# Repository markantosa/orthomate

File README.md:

# EPD 3D G6 — Orthomate

Battery-powered adaptive orthopedic insole controller. Redistributes plantar pressure in real-time using three micro linear stepper actuators driven by force sensor feedback. Includes a BLE companion Android app for live monitoring.

> **🏆 Winner — Top Course Project, EPD 3D Exhibition April 2026**

## Hardware at a glance

| Component | Detail |
|-----------|--------|
| MCU | ESP32-C6 SuperMini |
| Stepper drivers | 3× TMC2209 (STEP/DIR mode, ENN hardwired LOW on PCB) |
| Actuators | 3× micro linear bipolar stepper |
| Pressure sensors | 4× FSR (R1 1kΩ + C 100nF RC filter per channel, R2 10kΩ pull-down) |
| Display | 0.91" OLED (SSD1306, I2C) |
| Charger | TP4056 Type-C |
| Boost converter | XL6009 → 5 V system rail |
| Battery | 1S LiPo 2000–3000 mAh |
| User input | 1× momentary mode button |
| BLE | NimBLE-Arduino 2.5.0 — advertises as `EPD3DG6` |

## PCB placement

Orthomate uses two custom PCBs that work together inside a modified shoe:

**Controller PCB** — mounts in a controller module. Houses the ESP32-C6, three TMC2209 stepper drivers, TP4056 charger, XL6009 boost converter, and the 20-pin connector (J9) to the insole. The LiPo battery sits alongside it.

**Insole PCB** — sits directly underfoot inside the shoe. Hosts the three FSR pressure-sensing zones (metatarsal, arch, calcaneus) and the three micro linear stepper actuator assemblies. The actuators extend upward to redistribute localised plantar pressure. Connects back to the controller PCB via a 20-pin ribbon/wire harness.

## Exhibition highlights

### Final product

### ANSYS stress analysis

### Exhibition day

### Poster

### Downloadable resources

- [Orthomate Final Slides (PDF)](Exhibition%20Files%20and%20Photos/Orthomate%20Final%20Slides.pdf)
- [Orthomate Poster (PDF)](Exhibition%20Files%20and%20Photos/Orthomate%20Poster.pdf)

## Repository structure

```
orthomate/
├── Electronics Reference.txt           # Hardware design spec (v6.0)
├── BOM.txt                             # Bill of materials
├── firmware/
│   ├── main/                           # Full operational firmware (PlatformIO)
│   │   ├── platformio.ini
│   │   └── src/main.cpp
│   ├── ARDUINO IDE MAIN/               # Arduino IDE version of the full firmware
│   │   └── EPD3DG6_Main/EPD3DG6_Main.ino
│   ├── ARDUINO IDE APP TEST/           # Minimal Arduino IDE sketch for BLE app testing
│   │   └── sketch_apr14a/sketch_apr14a.ino
│   ├── stepper_test/                   # Single-axis stepper back-and-forth smoke test
│   ├── homing_test/                    # Blind homing: retract to min, extend to 12 mm
│   ├── button_test/                    # Button + OLED input test
│   └── oled_test/                      # OLED display test
├── android_app/                        # Kotlin/Compose BLE companion app
│   └── app/src/main/AndroidManifest.xml
├── Controller PCB KiCad Files/         # KiCad schematic + layout for controller PCB
├── Controller PCB Iterations/          # Gerber files from each revision (V2–V5)
├── Insole PCB KiCad Files/             # KiCad schematic + layout for insole PCB
├── Insole PCB Iterations/              # Gerber files from each revision
├── Exhibition Files and Photos/        # Exhibition media, poster, and slides
└── docs/
    ├── FIRMWARE_MAIN.md                # Detailed firmware walkthrough
    ├── FLASH_GUIDE.md                  # PlatformIO build & upload instructions
    ├── ANDROID_APP_GUIDE.md            # Android app build & sideload instructions
    └── TMC2209_CURRENT_TUNING.md
```

## Firmware — operational logic

The main firmware (`firmware/main/`) implements a full fitting cycle driven by one button:

```
DISCONNECTED ──[plug in]──► CONNECTED ──[btn]──► MEASURING
                                                      │ (auto)
                                                  MEASURED ──[btn]──► ACTUATING
                                                                           │ (auto)
                                                                         DONE ──[unplug]──► DISCONNECTED
                                                                         (insole retains shape)

On next plug-in with actuators extended:  DISCONNECTED ──► HOMING ──► CONNECTED
```

| Mode | Behaviour |
|------|-----------|
| **CONNECTED** | Idle; shows battery %, BLE status on OLED |
| **MEASURING** | Reads all 4 FSR channels, 7-sample median filter, computes relative load fractions |
| **ACTUATING** | Drives each actuator inversely proportional to region load — lowest load = largest extension |
| **DONE** | Holds position; unplug to use insole as-is |
| **HOMING** | Auto-triggered on reconnect when actuators are extended; retracts all to home |

Extension formula: $ext_i \propto (1 - r_i)$ where $r_i = F_i / \sum F$

## BLE — Android companion app

The ESP32 advertises a GATT service and notifies a JSON payload at ~4 Hz:

```json
{"fsr1": 42, "fsr2": 18, "fsr3": 75, "mode": "MEASURING", "batt": 67}
```

| BLE field | Value |
|-----------|-------|
| Device name | `EPD3DG6` |
| Service UUID | `4fa0c560-78a3-11ee-b962-0242ac120002` |
| Characteristic UUID | `4fa0c561-78a3-11ee-b962-0242ac120002` (NOTIFY + READ) |
| Notify rate | ~4 Hz (every 250 ms) |
| MTU | 185 bytes |

The Android app (`android_app/`) displays real-time FSR forces as animated colour circles, current mode, battery %, and BLE status. See [docs/ANDROID_APP_GUIDE.md](docs/ANDROID_APP_GUIDE.md) for build and install instructions.

## GPIO assignment (ESP32-C6 SuperMini, Hardware Ref v6.0)

| GPIO | Function |
|------|----------|
| 0 | FSR1 METATARSAL (ADC, 11 dB attenuation) |
| 1 | FSR2 ARCH (ADC, 11 dB attenuation) |
| 2 | FSR3 CALCANEUS (ADC, 11 dB attenuation) |
| 3 | FSR4 AUX (ADC, 11 dB attenuation) |
| 4 | MODE\_BUTTON (INPUT\_PULLUP) — boot-safe |
| 5 | VBAT\_SENSE (ADC1 ch5, 11 dB attenuation, 1:2 divider) |
| 6 | OLED SCL (I2C) |
| 7 | OLED SDA (I2C) |
| 14 | ACT3\_DIR ⚠ dead channel (stepper motor pad detached) |
| 15 | CONN\_DETECT (INPUT\_PULLDOWN) |
| 16 | ACT2\_STEP (arch actuator) |
| 17 | ACT2\_DIR (arch actuator) |
| 18 | ACT3\_STEP ⚠ dead channel (stepper motor pad detached) |
| 19 | ACT1\_DIR |
| 20 | ACT1\_STEP |

## Quick start

- **Flash firmware:** [docs/FLASH_GUIDE.md](docs/FLASH_GUIDE.md)
- **Install Android app:** [docs/ANDROID_APP_GUIDE.md](docs/ANDROID_APP_GUIDE.md)
- **Firmware internals:** [docs/FIRMWARE_MAIN.md](docs/FIRMWARE_MAIN.md)

## Design rules

- Charging and actuator operation are **mutually exclusive** — never simultaneous.
- Never start all 3 motors simultaneously — stagger motor starts by 75 ms.
- Sample FSRs only when motors are idle; use 7-sample median filtering with 4 ms settling per sample.
- ADC attenuation must be set to **11 dB** (`ADC_11db`) on all analog pins for correct readings at the operating voltage range.
- VBAT < 3.35 V → disable actuators; VBAT < 3.5 V → show low battery warning.
- OLED updates are content-cached — only redraws when text changes (prevents I2C writes during motor current spikes).

## License

MIT — see [LICENSE](LICENSE)

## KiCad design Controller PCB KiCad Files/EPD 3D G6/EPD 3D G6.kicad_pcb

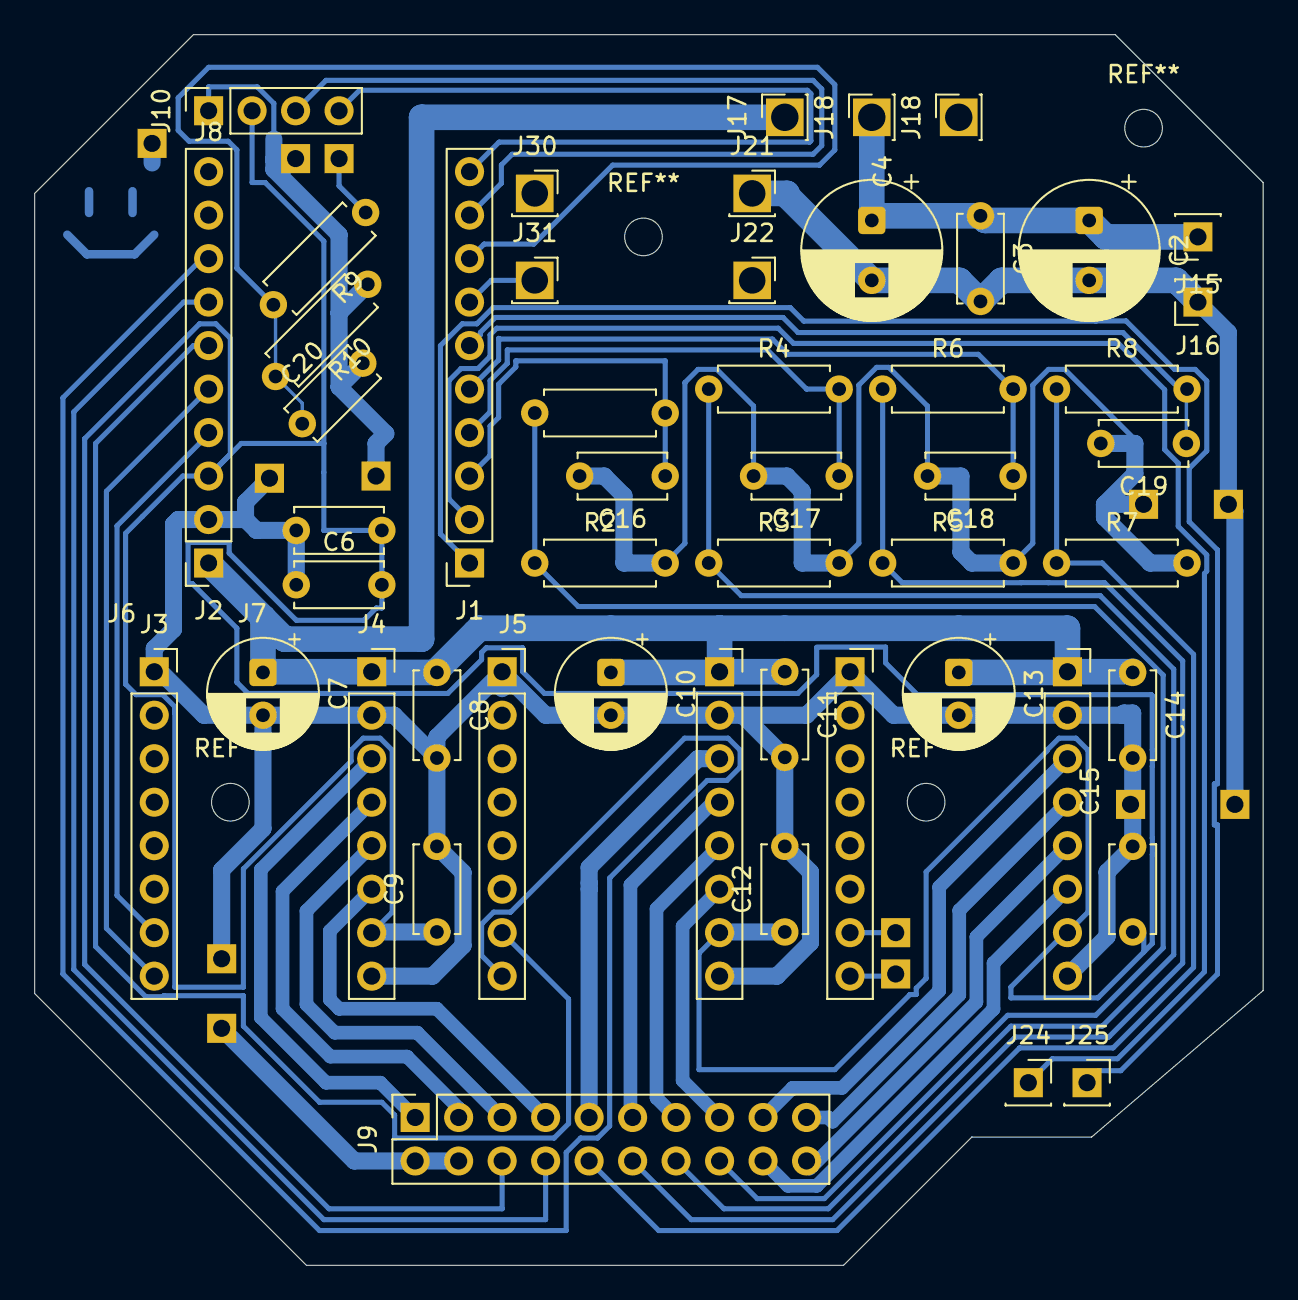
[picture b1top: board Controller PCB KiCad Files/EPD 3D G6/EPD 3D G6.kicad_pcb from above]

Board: 2 copper layers, 71.8 x 71.9 mm, 50 parts (0 on the bottom side), 34 nets.

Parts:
C2, C4: 470uF; CP_Radial_D8.0mm_P3.50mm
C3, C6, C8, C9, C11, C12, C14, C15, C16, C17, C18, C19, C20: 100nF; C_Disc_D5.0mm_W2.5mm_P5.00mm
C5: 10uF; C_Disc_D5.0mm_W2.5mm_P5.00mm
C7, C10, C13: 100uF; CP_Radial_D6.3mm_P2.50mm
J1: J_ESP32_L; PinSocket_1x10_P2.54mm_Vertical
J2: J_ESP32_R; PinSocket_1x10_P2.54mm_Vertical
J3: TMC2209_1_L; PinSocket_1x08_P2.54mm_Vertical
J4: TMC2209_1_R; PinSocket_1x08_P2.54mm_Vertical
J5: TMC2209_2_L; PinSocket_1x08_P2.54mm_Vertical
J6: TMC2209_2_R; PinSocket_1x08_P2.54mm_Vertical
J7: TMC2209_3_L; PinSocket_1x08_P2.54mm_Vertical
J8: TMC2209_3_R; PinSocket_1x08_P2.54mm_Vertical
J9: 20 PIN TO INSOLE; PinSocket_2x10_P2.54mm_Vertical
J10: OLED; PinSocket_1x04_P2.54mm_Vertical
J15: BOOST_OUT+; PinSocket_1x01_P2.54mm_Vertical
J16: BOOST_OUT-; PinSocket_1x01_P2.54mm_Vertical
J17: PWR+; PinSocket_1x01_P2.54mm_Vertical
J18, J18#2: PWR-; PinSocket_1x01_P2.54mm_Vertical
J21: BTN3; PinSocket_1x01_P2.54mm_Vertical
J22: BTN4; PinSocket_1x01_P2.54mm_Vertical
J24: ACT3_DIR; PinSocket_1x01_P2.54mm_Vertical
J25: ACT3_STEP; PinSocket_1x01_P2.54mm_Vertical
J30, J31: BTN1; PinSocket_1x01_P2.54mm_Vertical
R1, R4, R6, R8: 1k; R_Axial_DIN0207_L6.3mm_D2.5mm_P7.62mm_Horizontal
R2, R3, R5, R7: 10k; R_Axial_DIN0207_L6.3mm_D2.5mm_P7.62mm_Horizontal
R9, R10: 100k; R_Axial_DIN0207_L6.3mm_D2.5mm_P7.62mm_Horizontal

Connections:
3V3: C5.2, C6.2, C9.1, C12.1, C15.1, J2.3, J4.7, J6.7, J8.7, J9.6, J10.VCC
5V_SYS: C2.1, C3.1, C4.1, C7.1, C8.1, C10.1, C11.1, C13.1, C14.1, J2.1, J4.1, J6.1, J8.1, J15.1, J17.1, J18.1
ACT1_DIR: J2.5, J3.8
ACT1_OA1: J4.4, J9.3
ACT1_OA2: J4.3, J9.1
ACT1_OB1: J4.5, J9.5
ACT1_OB2: J4.6, J9.7
ACT1_STEP: J2.4, J3.7
ACT2_DIR: J2.8, J5.8
ACT2_OA1: J6.E, J9.11
ACT2_OA2: J6.3, J9.9
ACT2_OB1: J6.5, J9.13
ACT2_OB2: J6.6, J9.15
ACT2_STEP: J2.6, J5.7
ACT3_DIR: J1.2, J7.8, J24.1
ACT3_OA1: J8.4, J9.19
ACT3_OA2: J8.3, J9.17
ACT3_OB1: J8.5, J9.20
ACT3_OB2: J8.6, J9.18
ACT3_STEP: J1.1, J7.7, J25.1
CONN_DETECT: J2.7, J9.8
FSR1: J9.16, R1.1, R2.1
FSR1_ADC: C16.1, J1.3, R1.2
FSR2: J9.14, R3.1, R4.1
FSR2_ADC: C17.1, J1.E, R4.2
FSR3: J9.12, R5.1, R6.1
FSR3_ADC: C18.1, J1.5, R6.2
FSR4: J9.10, R7.1, R8.1
FSR4_ADC: C19.1, J1.6, R8.2
GND: C2.2, C3.2, C4.2, C5.1, C6.1, C7.2, C8.2, C9.2, C10.2, C11.2, C12.2, C13.2, C14.2, C15.2, C16.2, C17.2, C18.2, C19.2, C20.2, J2.2, J3.ACT1_EN, J4.2, J4.8, J5.ACT2EN, J6.2, J6.8, J7.ACT3_EN, J8.2, J8.8, J9.2, J9.4, J10.GND (Pin_1_GND), J16.1, J21.1, R2.2, R3.2, R5.2, R7.2, R10.1
MODE_BTN: J1.7, J30.1, J31.1
OLED_SCL: J1.9, J10.OLED_SCL
OLED_SDA: J1.10, J10.OLED_SDA
VBAT_SENSE: C20.1, J1.8, R9.2, R10.2

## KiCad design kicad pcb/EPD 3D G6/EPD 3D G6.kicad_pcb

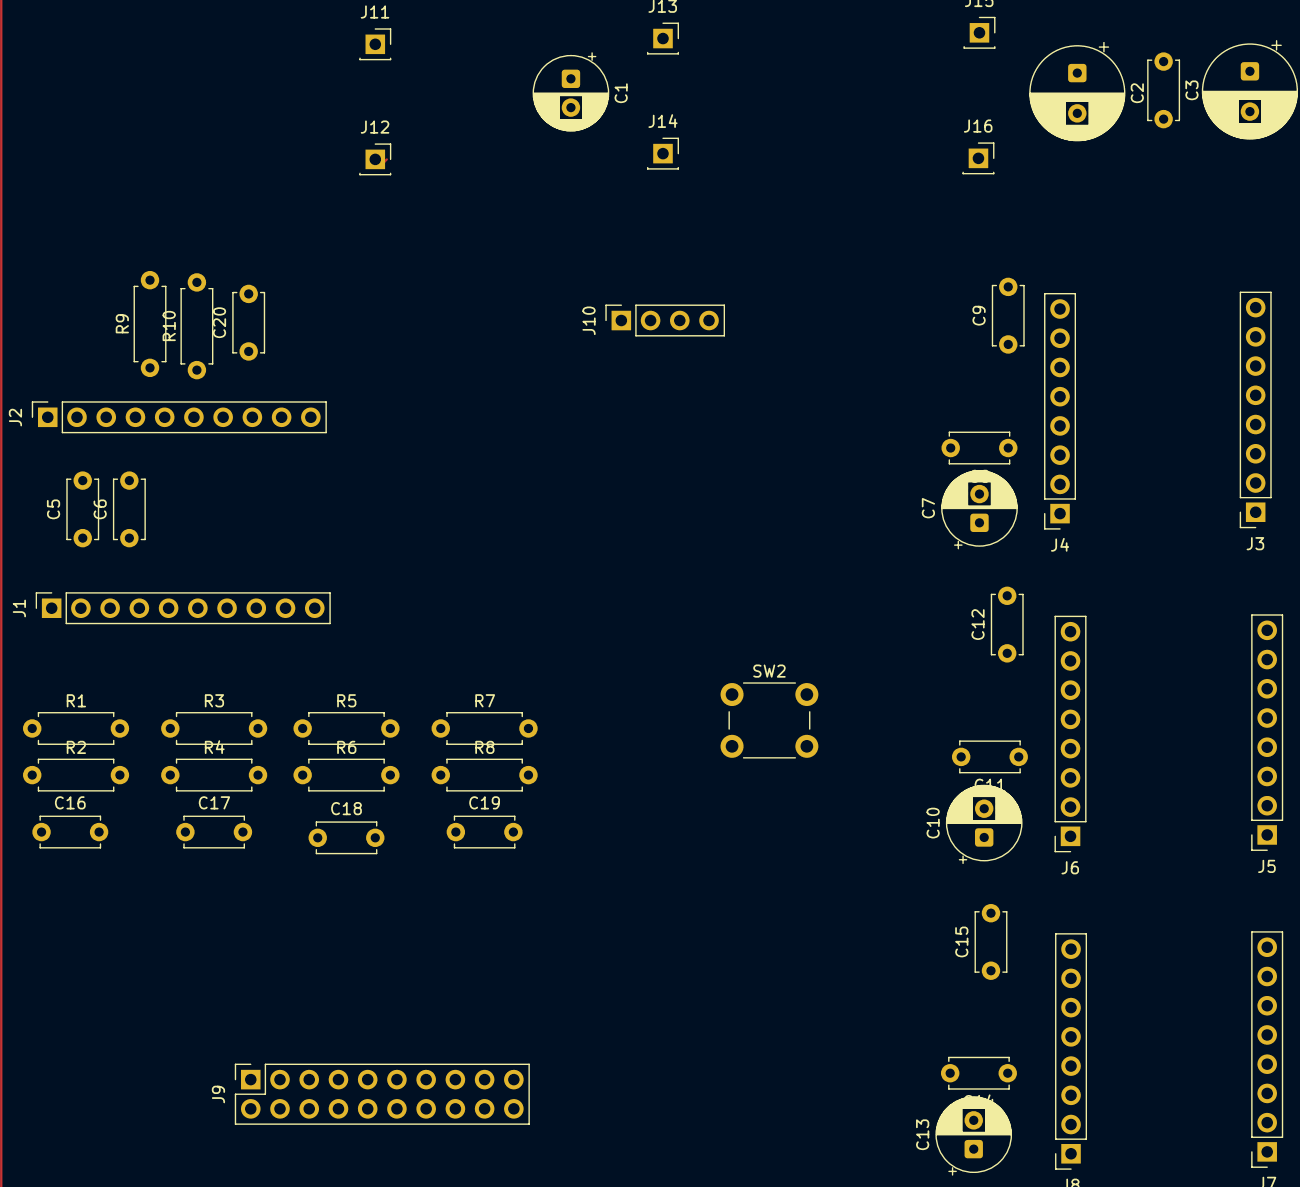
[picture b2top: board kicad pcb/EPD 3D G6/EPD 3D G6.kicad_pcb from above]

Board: 2 copper layers, 47 parts (0 on the bottom side), 13 nets.

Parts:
C1, C7, C10, C13: 100uF; CP_Radial_D6.3mm_P2.50mm
C2, C4: 470uF; CP_Radial_D8.0mm_P3.50mm
C3, C6, C8, C9, C11, C12, C14, C15, C16, C17, C18, C19, C20: 100nF; C_Disc_D5.0mm_W2.5mm_P5.00mm
C5: 10uF; C_Disc_D5.0mm_W2.5mm_P5.00mm
J1: J_ESP32_L; PinSocket_1x10_P2.54mm_Vertical
J2: J_ESP32_R; PinSocket_1x10_P2.54mm_Vertical
J3: TMC2209_1_L; PinSocket_1x08_P2.54mm_Vertical
J4: TMC2209_1_R; PinSocket_1x08_P2.54mm_Vertical
J5: TMC2209_2_L; PinSocket_1x08_P2.54mm_Vertical
J6: TMC2209_2_R; PinSocket_1x08_P2.54mm_Vertical
J7: TMC2209_3_L; PinSocket_1x08_P2.54mm_Vertical
J8: TMC2209_3_R; PinSocket_1x08_P2.54mm_Vertical
J9: 20 PIN TO INSOLE; PinSocket_2x10_P2.54mm_Vertical
J10: OLED; PinSocket_1x04_P2.54mm_Vertical
J11: BAT+; PinSocket_1x01_P2.54mm_Vertical
J12: BAT-; PinSocket_1x01_P2.54mm_Vertical
J13: BOOST_IN+; PinSocket_1x01_P2.54mm_Vertical
J14: BOOST_IN-; PinSocket_1x01_P2.54mm_Vertical
J15, J16: BOOST_OUT+; PinSocket_1x01_P2.54mm_Vertical
R1, R4, R6, R8: 1k; R_Axial_DIN0207_L6.3mm_D2.5mm_P7.62mm_Horizontal
R2, R3, R5, R7: 10k; R_Axial_DIN0207_L6.3mm_D2.5mm_P7.62mm_Horizontal
R9, R10: 100k; R_Axial_DIN0207_L6.3mm_D2.5mm_P7.62mm_Horizontal
SW2: SW_Push; SW_PUSH_6mm

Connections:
3V3: C5.2, C6.2, C9.1, C12.1, C15.1
5V_SYS: C2.1, C3.1, C4.1, C7.1, C8.1, C10.1, C11.1, C13.1, C14.1
FSR1: J9.5, R1.1, R2.1
FSR1_ADC: C16.1, R1.2
FSR2: J9.6, R3.1, R4.1
FSR2_ADC: C17.1, R4.2
FSR3: J9.7, R5.1, R6.1
FSR3_ADC: C18.1, R6.2
FSR4: J9.8, R7.1, R8.1
FSR4_ADC: C19.1, R8.2
GND: C2.2, C3.2, C4.2, C5.1, C6.1, C7.2, C8.2, C9.2, C10.2, C11.2, C12.2, C13.2, C14.2, C15.2, C16.2, C17.2, C18.2, C19.2, C20.2, J9.3, J9.4, R2.2, R3.2, R5.2, R7.2, R10.1, SW2.2
VBAT: C1.1, R9.1
VBAT_SENSE: C20.1, R9.2, R10.2

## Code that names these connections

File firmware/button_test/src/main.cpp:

/**
 * button_test — EPD 3D G6
 *
 * MODE button (GPIO4, INPUT_PULLUP, active LOW) triggers a sequence:
 *   Press → extend 5 s → retract 5 s → stop
 *
 * Wiring (Electronics Reference v5.0):
 *   GPIO 20 → ACT1_STEP
 *   GPIO 19 → ACT1_DIR
 *   GPIO 7  → OLED SDA
 *   GPIO 6  → OLED SCL
 *   GPIO 4  → MODE_BTN  (INPUT_PULLUP — do NOT hold at boot)
 *   ENN     → GND       (driver always enabled)
 */

#include <Arduino.h>
#include <Wire.h>
#include <Adafruit_GFX.h>
#include <Adafruit_SSD1306.h>

// ── Pins ─────────────────────────────────────────────────────────────────────
static constexpr uint8_t PIN_STEP = 20;
static constexpr uint8_t PIN_DIR  = 19;
static constexpr uint8_t PIN_BTN  = 4;   // MODE_BTN, active LOW
static constexpr uint8_t PIN_SDA  = 7;
static constexpr uint8_t PIN_SCL  = 6;

// ── OLED ─────────────────────────────────────────────────────────────────────
static Adafruit_SSD1306 gDisplay(128, 64, &Wire, -1);

static void oledShow(const char* status) {
    gDisplay.clearDisplay();
    gDisplay.setTextColor(SSD1306_WHITE);
    gDisplay.setTextSize(2);
    gDisplay.setCursor(0, 24);
    gDisplay.println(status);
    gDisplay.display();
}

// ── Motion ───────────────────────────────────────────────────────────────────
static constexpr uint32_t STEP_PULSE_US   = 20;    // step HIGH pulse width (µs)
static constexpr uint32_t STEP_START_US   = 16000; // starting step period (~60 steps/s)
static constexpr uint32_t STEP_MIN_US     = 4000;  // top-speed step period (~250 steps/s)
static constexpr uint32_t ACCEL_STEPS     = 200;   // steps to ramp from start to top speed
static constexpr uint32_t RUN_DURATION_MS = 5000;  // extend/retract time (ms)

// ── State ────────────────────────────────────────────────────────────────────
enum class RunState { IDLE, EXTENDING, RETRACTING };

static RunState gState        = RunState::IDLE;
static uint32_t gPhaseStart   = 0;
static uint32_t gLastStepUs   = 0;
static uint32_t gStepCount    = 0;   // steps taken in current phase (for ramp)
static bool     gLastBtn      = false;

// ── Helpers ──────────────────────────────────────────────────────────────────
static void motorStart(bool forward) {
    digitalWrite(PIN_DIR, forward ? HIGH : LOW);
    delayMicroseconds(100);
    gPhaseStart = millis();
    gLastStepUs = micros();
    gStepCount  = 0;
    oledShow(forward ? "EXTENDING" : "RETRACTING");
    Serial.printf("%s for %lus\n", forward ? "→ Extending" : "← Retracting", RUN_DURATION_MS / 1000);
}

static void motorStop() {
    oledShow("STOPPED");
    Serial.println("■ Stopped");
}

static void tickMotor() {
    // Linear ramp: interpolate period from STEP_START_US down to STEP_MIN_US
    uint32_t period = (gStepCount < ACCEL_STEPS)
        ? STEP_START_US - (uint32_t)((STEP_START_US - STEP_MIN_US) * gStepCount / ACCEL_STEPS)
        : STEP_MIN_US;

    uint32_t now = micros();
    if (now - gLastStepUs >= period) {
        digitalWrite(PIN_STEP, HIGH);
        delayMicroseconds(STEP_PULSE_US);
        digitalWrite(PIN_STEP, LOW);
        gLastStepUs = micros();
        gStepCount++;
    }
}

// ── Arduino entry points ─────────────────────────────────────────────────────
void setup() {
    Serial.begin(115200);
    delay(500);
    Serial.println("EPD 3D G6 — button test");
    Serial.printf("  Press -> extend %lus -> retract %lus\n", RUN_DURATION_MS / 1000, RUN_DURATION_MS / 1000);

    Wire.begin(PIN_SDA, PIN_SCL);
    gDisplay.begin(SSD1306_SWITCHCAPVCC, 0x3C);
    oledShow("STOPPED");

    pinMode(PIN_STEP, OUTPUT);
    pinMode(PIN_DIR,  OUTPUT);
    pinMode(PIN_BTN,  INPUT_PULLUP);

    digitalWrite(PIN_STEP, LOW);
    digitalWrite(PIN_DIR,  LOW);
}

void loop() {
    const bool pressed = (digitalRead(PIN_BTN) == LOW);

    switch (gState) {

        // ── Waiting for button press ──────────────────────────────────────────
        case RunState::IDLE:
            if (pressed && !gLastBtn) {  // rising edge only
                motorStart(true);
                gState = RunState::EXTENDING;
            }
            break;

        // ── Extending 5 s ────────────────────────────────────────────────────
        case RunState::EXTENDING:
            tickMotor();
            if (millis() - gPhaseStart >= RUN_DURATION_MS) {
                motorStart(false);
                gState = RunState::RETRACTING;
            }
            break;

        // ── Retracting 5 s ───────────────────────────────────────────
        case RunState::RETRACTING:
            tickMotor();
            if (millis() - gPhaseStart >= RUN_DURATION_MS) {
                motorStop();
                gState = RunState::IDLE;
            }
            break;
    }

    gLastBtn = pressed;
}

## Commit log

2026-04-01 Initial commit — hardware ref v4.1, operational firmware, LICENSE
2026-04-01 Add OLED test firmware (128x64 SSD1306, SCL=GPIO6, SDA=GPIO7)
2026-04-01 Add TMC2209 current limit tuning guide
2026-04-01 Add schematic framework (Phase A) - all 9 blocks, power rails, pin map, notes
2026-04-01 Reorganise schematic global labels for clean left-to-right power/signal flow
    - Power rails (VBAT, 5V_SYS, 3V3) moved to top of each block (Y=12-36)
    - ESP32 Block 3: inputs left side Y=30-90 (10mm steps), outputs right Y=30-110
    - TMC blocks 4A/4B/4C: power+signals stacked top-to-bottom within each block band
    - FSR/VBAT_SENSE/OLED/UI labels spread across full block height (no clustering)
    - Fixed label shapes: Block 3 input pins now correctly use 'input' shape (were 'output')
    - 48 global labels total, all named nets connect correctly
2026-04-01 Fix label positions: place all global_labels on block boundary edges
    Each label now sits exactly on its block's border (X=54/58/110/114/188/192/108/2)
    rather than floating in the middle of the sheet.
    - B1 VBAT output: right edge X=54
    - B2 VBAT in left X=58, 5V_SYS out right X=110
    - B3 ESP32: power at Y=9 top edge, 7 inputs on left X=114, 9 outputs on right X=188
    - B4A/4B/4C TMC: 5 inputs each on left X=192, distributed within Y bands
2026-04-02 Update all docs and firmware to Electronics Reference v5.0
    GPIO changes (v4.1 -> v5.0):
    VBAT_SENSE: GPIO5 -> GPIO6
    STEPPER_ENN: GPIO4 -> GPIO7
    ACT1 STEP: GPIO6 -> GPIO20
    ACT1 DIR: GPIO7 -> GPIO19
    ACT2 STEP: GPIO12 -> GPIO18
2026-04-02 Add CONN_DETECT on GPIO5 to Electronics Reference v5.0
2026-04-02 Update connector J_MAIN pinout: pin 2 CONN_DETECT loopback detect, gitignore KiCad backups/cache
2026-04-03 Add FIRMWARE_MAIN doc, rework state machine disconnect-to-use, remove fix_labels.ps1
2026-04-03 Remove KiCad .history embedded repo from tracking
2026-04-03 Ignore KiCad .history folder
2026-04-07 Add homing_test firmware; tune stepper_test; update KiCad; update docs
2026-04-09 Add V2 PCB gerbers; remove kicad pcb from repo; update .gitignore
2026-04-13 Add V3 and V4 PCB gerber files
2026-04-13 docs: update pinout to v6.0 (ENN to GND, OLED SCL=GPIO6 SDA=GPIO7, VBAT=GPIO15, new J9 connector)
2026-04-13 docs: reassign CONN_DETECT to GPIO15, VBAT_SENSE to GPIO5 (ADC-capable)
2026-04-14 feat: add BLE telemetry to firmware and Android companion app
    - firmware/main: add NimBLE-Arduino BLE server
    - advertises as EPD3DG6
    - notifies JSON payload {fsr1,fsr2,fsr3,mode,batt} at ~4 Hz
    - fix PIN_VBAT=5, PIN_CONN=15 per hardware ref v6.0
    - android_app: new Kotlin/Compose BLE companion app
    - displays relative FSR forces (animated colour+size circles)
2026-04-15 docs: update README, FIRMWARE_MAIN, FLASH_GUIDE for BLE, OLED status bar, ADC attenuation fix
    - README: add BLE section with UUIDs/payload, Android app quick-start, updated
    hardware table (NimBLE-Arduino 2.5.0), corrected state machine (HOMING state,
    DISCONNECTED flow), updated repo structure, design rules (ADC_11db note)
    - FIRMWARE_MAIN: add Section 8 (BLE - NimBLE 2.x API, setupBLE, JSON payload,
    globals, callback signatures), Section 9 (OLED status bar - showOLEDWithStatus,
    per-state table), update Section 5 (battery) with ADC_11db attenuation fix and
2026-04-15 rebrand: Pumped Up Kicks -> Orthomate; firmware BLE snap field; Android app updates
    - README.md, Electronics Reference.txt: renamed product to Orthomate
    - firmware/main/src/main.cpp: add gMeasuredLoad[] snapshot saved at end of
    doMeasure(); bleNotify() sends snapshot during ACTUATING/DONE with snap=1,
    live gRelLoad during all other states with snap=0; updated JSON payload comment
    - android_app: Gemini-applied changes (Orthomate branding, snap field support,
    FSR snapshot display/storage, Gemini API analysis feature, updated BLE parsing)
2026-04-22 Add Arduino IDE main firmware, KiCad files for controller and insole PCBs, reorganize PCB iterations, update main firmware and app assets
2026-04-23 Initial commit: Added Gemini 2.5 & BLE support
2026-04-23 Cleanup: remove all ignored files from tracking
2026-04-24 Add exhibition media, update README with photos/PCB placement, fix GPIO table, update BOM, tighten .gitignore
2026-04-24 Update project award details in README
2026-05-03 Add Insole 3D model photo, resize exhibition images side-by-side in README
